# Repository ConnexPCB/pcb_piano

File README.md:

# pcb_piano
PCB with cap touch buttons that activate frequency generator

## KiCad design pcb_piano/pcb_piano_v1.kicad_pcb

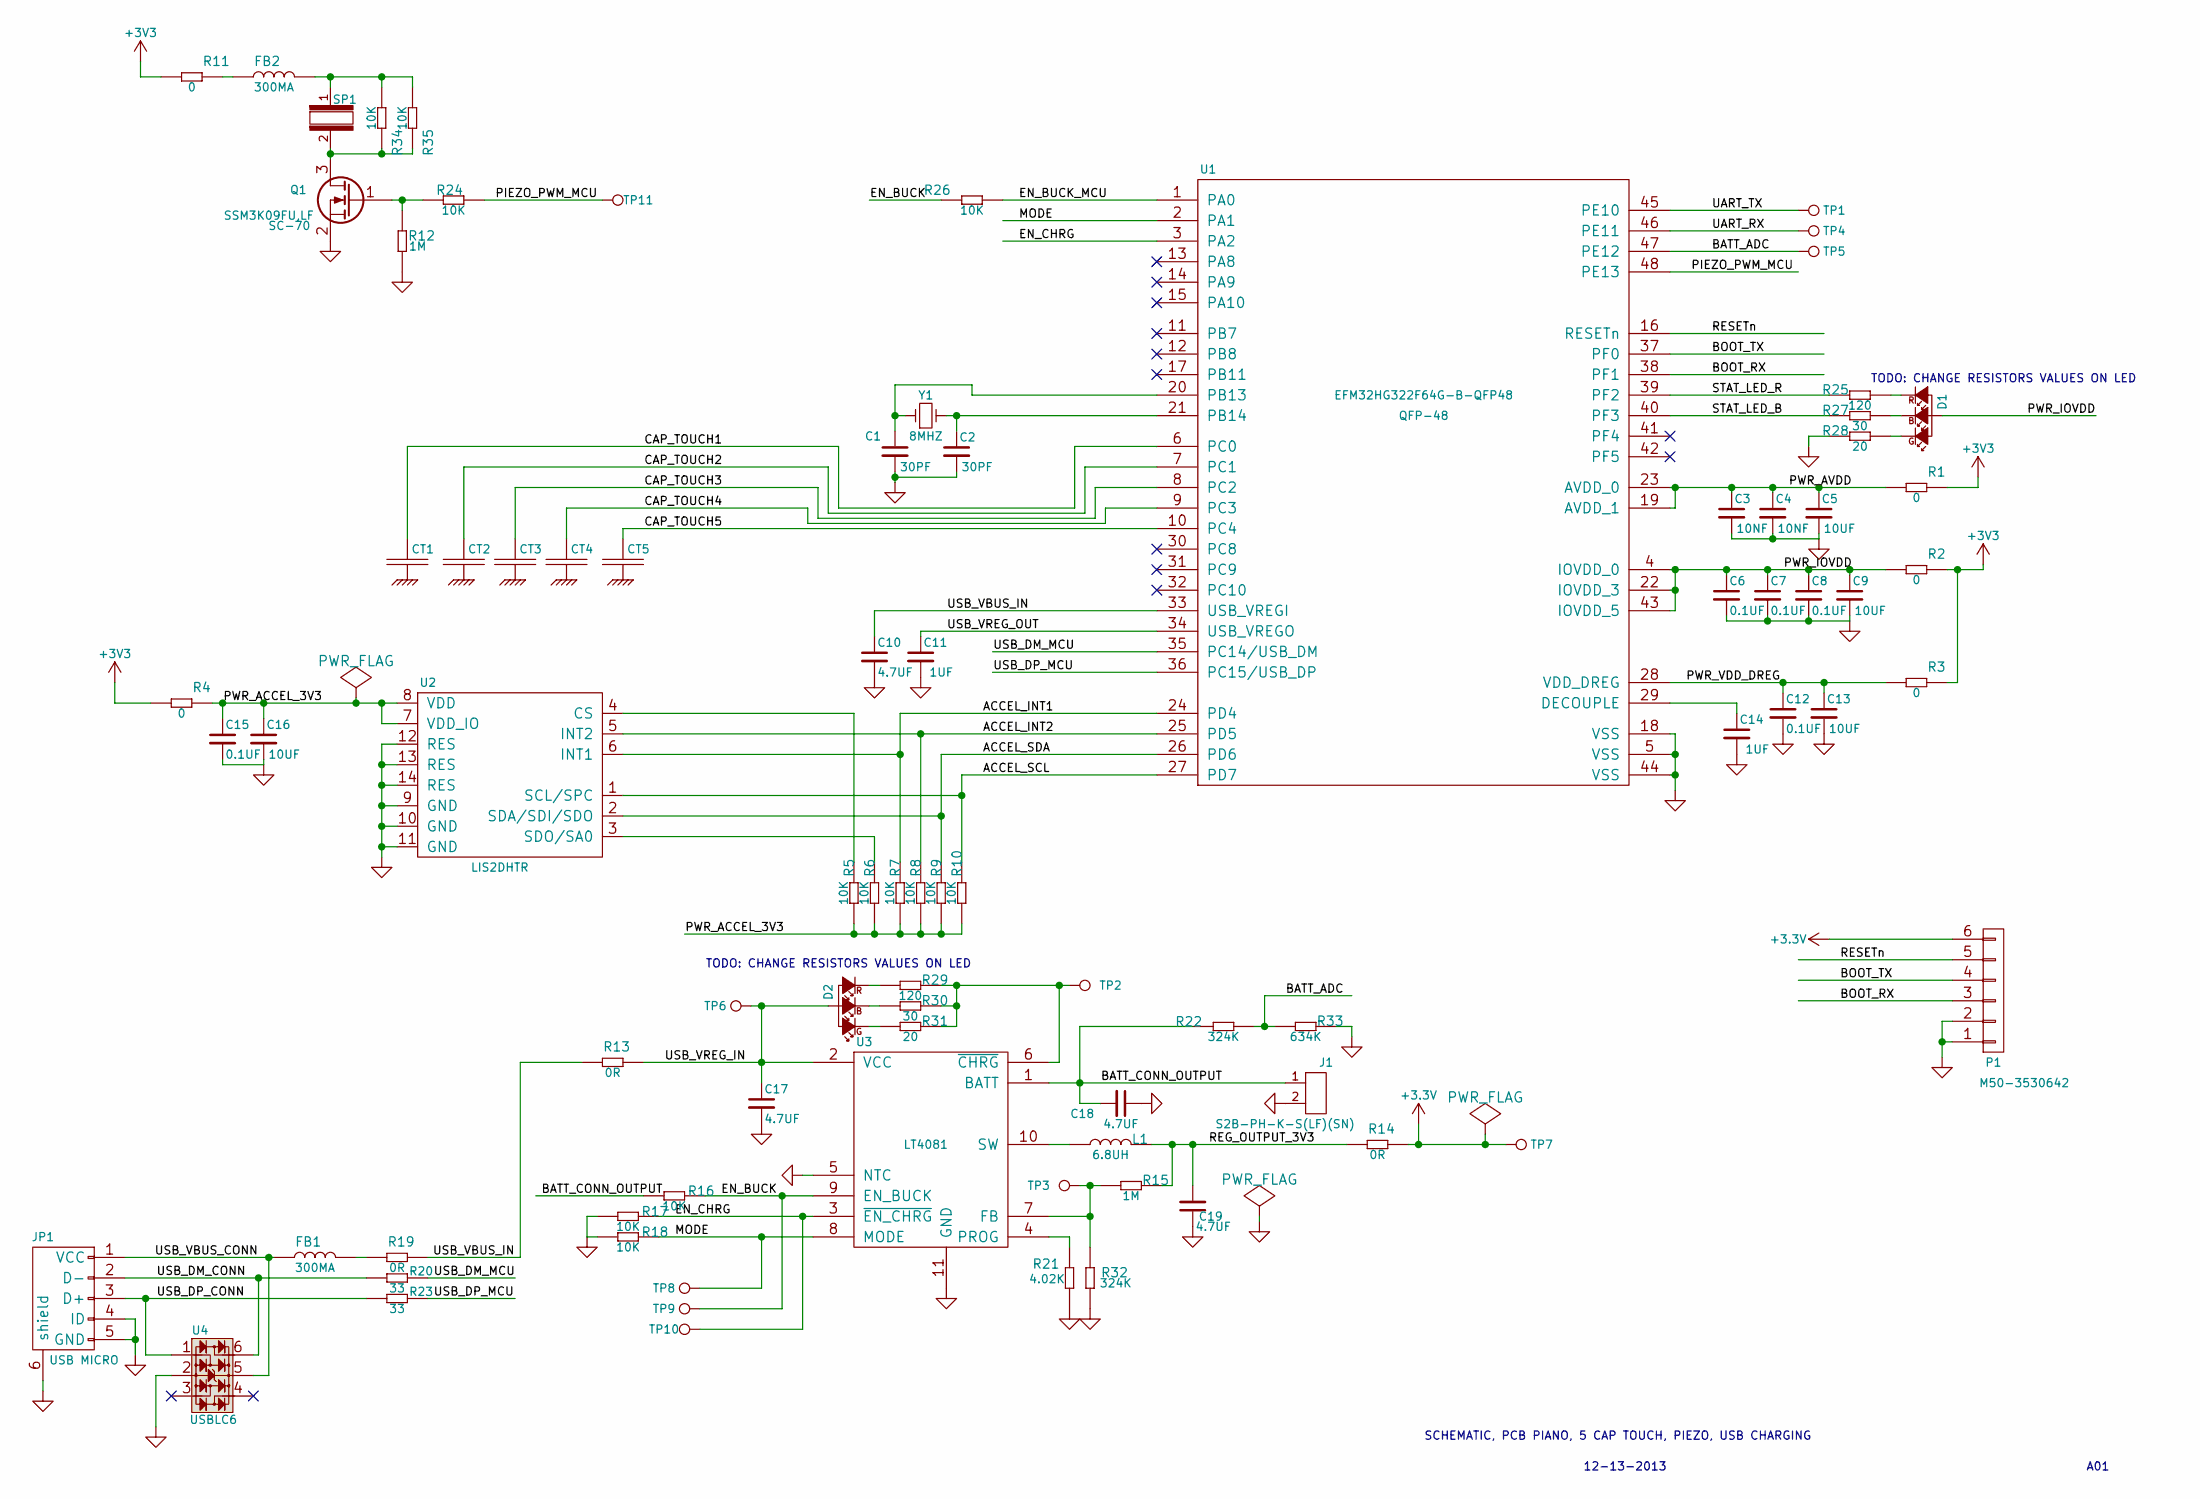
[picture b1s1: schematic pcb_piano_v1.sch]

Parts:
C1, C2: CONNEX-SMD-CAP-30PF-0402; C_0402; VOLTAGE 25V; MPN GRM1555C1E300JA01D
C3, C4: CONNEX-SMD-CAP-10NF-0402; C_0402; MPN GRM155R71C103KA01D
C5, C9, C13, C16: CONNEX-SMD-CAP-10UF-0402; C_0402; VOLTAGE 6.3V; MPN GRJ155R60J106ME11D
C6, C7, C8, C12, C15: CONNEX-SMD-CAP-100NF-0402; C_0402; MPN GRM155R71E104KE14D
C10, C17, C18, C19: CONNEX-SMD-CAP-4700NF-0603; C_0603; MPN GRM188R60J475ME19D
C11, C14: CONNEX-SMD-CAP-1UF-0402; C_0402; VOLTAGE 35V; MPN GRM155R6YA105KE11J
CT1, CT2, CT3, CT4, CT5: CONNEX-CAPTOUCH-BUTTON-SINGLE; CONNEX-CAPTOUCH-SINGLE-BUTTON-15MM; MPN NA
D1, D2: LED_RGB_SMLP34RGB1W3; led_0404_SMLP34RGB1W3; MPN SMLP34RGB1W3
FB1, FB2: CONNEX-SMD-FERRITE-BEAD-300MA-BLM15AG102SN1D; L_0402; MPN BLM15AG102SN1D
J1: CONNEX_CONN_2PIN_KEYED; CONNEX_CONN-2POS-KEYED-S2B-PH-K-S; MPN S2B-PH-K-S(LF)(SN)
JP1: connex_usb_micro_b_10103594-0001LF; USB_Micro-B_10103594-0001LF; MPN 10118194-0001LF
L1: CONNEX-SMD-INDUCTOR-6R8M-0603; L_0603; MPN GLFR1608T6R8M-LR
P1: CONN_01X06_M50-3530642; Pin_Header_Straight_1x06; MPN M50-3530642
Q1: Q_NMOS_SSM3K09FULF; SC-70; MPN SSM3K09FU,LF
R1, R2, R3, R4, R11: CONNEX-SMD-RES-0-0603; R_0603; MPN CRCW06030000Z0EAHP
R5, R6, R7, R8, R9, R10, R24, R34, R35: CONNEX-SMD-RES-10K-0603; R_0603; MPN CRCW060310K0FKEAHP
R12, R15: CONNEX-SMD-RES-1M-0603; R_0603; MPN RCG06031M00FKEA
R13, R14, R19: SMD-RES-0R-1_4W_0603_; R_0603; MPN CRCW06030000Z0EAHP
R16, R17, R18, R26: SMD-RES-10K-1%-1_10W_0603_; R_0603
R20, R23: CONNEX-SMD-RES-33-0402; R_0402; MPN ERJ-2RKF33R0X
R21: CONNEX-SMD-RES-4K02-0603; R_0603; MPN CRCW06034K02FKEA
R22, R32: CONNEX-SMD-RES-324K-0402; R_0402; MPN RC0402FR-07324KL
R25, R29: CONNEX-SMD-RES-120-0603; R_0603; MPN CRCW0603120RJNEA
R27, R30: CONNEX-SMD-RES-30-0603; R_0603; MPN CRCW060330R0JNEA
R28, R31: CONNEX-SMD-RES-20-0603; R_0603; MPN CRCW060320R0JNEA
R33: CONNEX-SMD-RES-634k-0402; R_0402; MPN ERJ-2RKF6343X
SP1: connex-piezo-4khz-AT-2440-TWT-R; CONNEX-PIEZO-AT-2440-TWT-R; MPN AT-2440-TWT-R
TP1, TP2, TP3, TP4, TP5, TP6, TP7, TP8, TP9, TP10, TP11: test_point_smt; TEST_POINT_SMD_50MIL; MPN na
U1: connex_EFM32HG322F64G-B-QFP48; TQFP-48_7x7mm_Pitch0.5mm; MPN EFM32HG322F64G-B-QFP48
U2: connex-accel-LIS2DHTR; CONNEX_LGA-14_2MMX2MM; MPN LIS2DHTR
U3: CONNEX_REGUL_LT4081; CONNEX_DFN_10PIN_3MMX3MM; MPN LTC4081EDD#PBF
U4: CONNEX-DIODE-TVS-USB-USBLC6-4SC6Y; SOT-23-6; MPN USBLC6-4SC6Y
Y1: Crystal_8MHZ_ABM3B-8.000MHZ-B2-T; CONNEX_CRYSTAL_4SMD_32X50; MPN ABM3B-8.000MHZ-B2-T

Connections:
/ACCEL_INT1: R7.2, U1.24 (PD4), U2.6 (INT1)
/ACCEL_INT2: R8.2, U1.25 (PD5), U2.5 (INT2)
/ACCEL_SCL: R10.2, U1.27 (PD7), U2.1 (SCL/SPC)
/ACCEL_SDA: R9.2, U1.26 (PD6), U2.2 (SDA/SDI/SDO)
/BATT_ADC: R22.1, R33.1, TP5.1, U1.47 (PE12)
/BATT_CONN_OUTPUT: C18.2, J1.1, R16.2, R22.2, U3.1 (BATT)
/BOOT_RX: P1.3, U1.38 (PF1)
/BOOT_TX: P1.4, U1.37 (PF0)
/CAP_TOUCH1: CT1.1, U1.6 (PC0)
/CAP_TOUCH2: CT2.1, U1.7 (PC1)
/CAP_TOUCH3: CT3.1, U1.8 (PC2)
/CAP_TOUCH4: CT4.1, U1.9 (PC3)
/CAP_TOUCH5: CT5.1, U1.10 (PC4)
/EN_BUCK: R16.1, R26.2, TP9.1, U3.9 (EN_BUCK)
/EN_BUCK_MCU: R26.1, U1.1 (PA0)
/EN_CHRG: R17.1, TP10.1, U1.3 (PA2), U3.3 (~EN_CHRG~)
/MODE: R18.1, TP8.1, U1.2 (PA1), U3.8 (MODE)
/PIEZO_PWM_MCU: R24.1, TP11.1, U1.48 (PE13)
/PWR_ACCEL_3V3: C15.1, C16.1, R4.2, R5.1, R6.1, R7.1, R8.1, R9.1, R10.1, U2.7 (VDD_IO), U2.8 (VDD)
/PWR_AVDD: C3.1, C4.1, C5.1, R1.1, U1.19 (AVDD_1), U1.23 (AVDD_0)
/PWR_IOVDD: C6.1, C7.1, C8.1, C9.1, D1.1, R2.1, U1.4 (IOVDD_0), U1.22 (IOVDD_3), U1.43 (IOVDD_5)
/PWR_VDD_DREG: C12.1, C13.1, R3.1, U1.28 (VDD_DREG)
/REG_OUTPUT_3V3: C19.2, L1.2, R14.1, R15.2
/RESETn: P1.5, U1.16 (RESETn)
/STAT_LED_B: R27.2, U1.40 (PF3)
/STAT_LED_R: R25.2, U1.39 (PF2)
/UART_RX: TP4.1, U1.46 (PE11)
/UART_TX: TP1.1, U1.45 (PE10)
/USB_DM_CONN: JP1.2 (D-), R20.1, U4.6 (IO4)
/USB_DM_MCU: R20.2, U1.35 (PC14/USB_DM)
/USB_DP_CONN: JP1.3 (D+), R23.1, U4.1 (IO1)
/USB_DP_MCU: R23.2, U1.36 (PC15/USB_DP)
/USB_VBUS_CONN: FB1.1, JP1.1 (VCC), U4.5 (VBUS)
/USB_VBUS_IN: C10.1, R13.1, R19.2, U1.33 (USB_VREGI)
/USB_VREG_IN: C17.1, D2.1, R13.2, TP6.1, U3.2 (VCC)
/USB_VREG_OUT: C11.1, U1.34 (USB_VREGO)
GND: C1.2, C2.2, C3.2, C4.2, C5.2, C6.2, C7.2, C8.2, C9.2, C10.2, C11.2, C12.2, C13.2, C14.2, C15.2, C16.2, C17.2, C18.1, C19.1, J1.2, JP1.4 (ID), JP1.5 (GND), JP1.6 (shield), P1.1, P1.2, Q1.2 (S), R12.2, R17.2, R18.2, R21.1, R28.2, R32.2, R33.2, U1.5 (VSS), U1.18 (VSS), U1.44 (VSS), U2.9 (GND), U2.10 (GND), U2.11 (GND), U2.12 (RES), U2.13 (RES), U2.14 (RES), U3.5 (NTC), U3.11 (GND), U4.2 (GND)
unnamed: C1.1, U1.20 (PB13), Y1.1
unnamed: C2.1, U1.21 (PB14), Y1.3
unnamed: C14.1, U1.29 (DECOUPLE)
unnamed: D1.2 (R), R25.1
unnamed: D1.3 (B), R27.1
unnamed: D1.4 (G), R28.1
unnamed: D2.2 (R), R29.1
unnamed: D2.3 (B), R30.1
unnamed: D2.4 (G), R31.1
unnamed: FB1.2, R19.1
unnamed: FB2.1, R11.2
unnamed: FB2.2, R34.1, R35.1, SP1.1
unnamed: L1.1, U3.10 (SW)
unnamed: Q1.1 (G), R12.1, R24.2
unnamed: Q1.3 (D), R34.2, R35.2, SP1.2
unnamed: R5.2, U2.4 (CS)
unnamed: R6.2, U2.3 (SDO/SA0)
unnamed: R15.1, R32.1, TP3.1, U3.7 (FB)
unnamed: R21.2, U3.4 (PROG)
unnamed: R29.2, R30.2, R31.2, TP2.1, U3.6 (~CHRG~)

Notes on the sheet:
SCHEMATIC, PCB PIANO, 5 CAP TOUCH, PIEZO, USB CHARGING
12-13-2013
A01
TODO: CHANGE RESISTORS VALUES ON LED

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
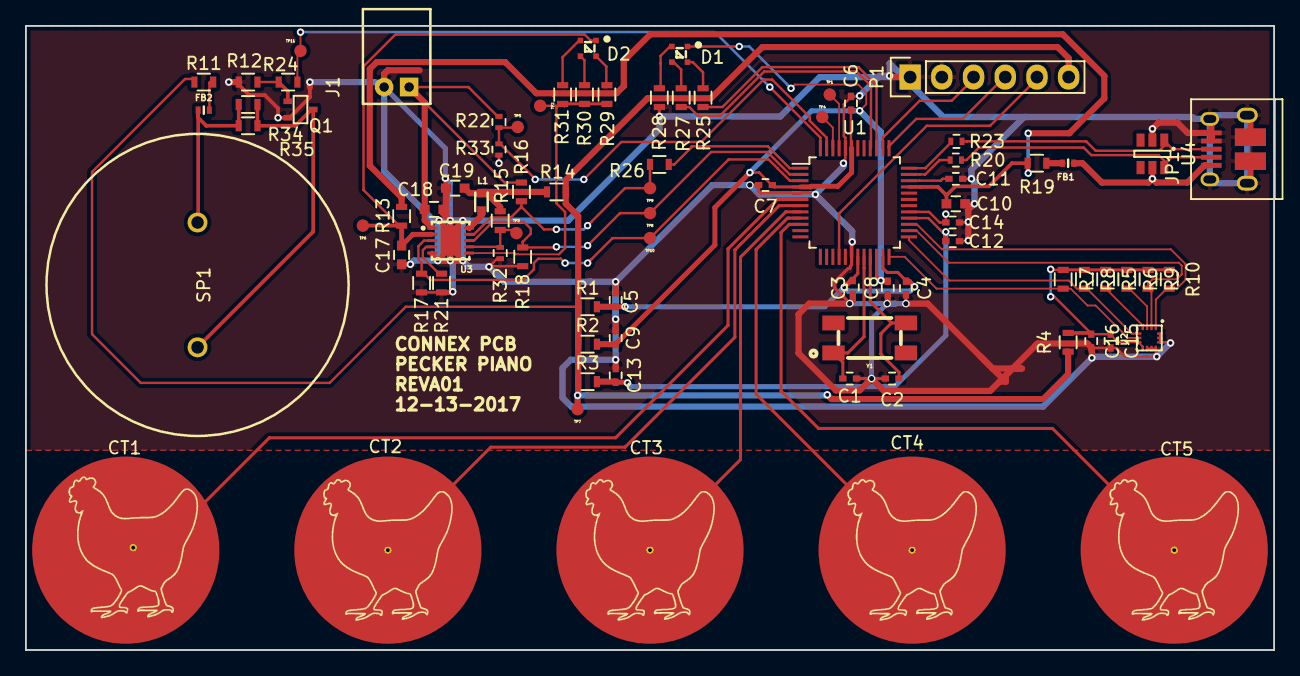
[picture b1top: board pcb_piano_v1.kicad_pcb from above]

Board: 2 copper layers, 100.0 x 50.0 mm, 85 parts (0 on the bottom side), 58 nets.

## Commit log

2017-12-12 Created kicad project for pcb_piano. Added connexPCB_libs submodule.
2017-12-13 Progress on schematic. Added happy gecko, regulator, and cap touch
2017-12-14 Added usb charging, ferrite bead, and piezo, began layout
2017-12-29 Pushed Version 1 hardware
2018-01-07 Mostly functional circular buffer with pwm. Though still has issues....
2018-01-07 Changed over to cpp files, created template for circular buffer
2018-01-13 Updated git ignore to be C and KiCAD
2018-01-13 Working version with PWM using DMA
2018-01-14 Note initialization to use sinusoid, and autoconfigure frequency based on PWM frequency (20khz)
2018-01-14 Cleaned up code from the previous debugging
2018-01-15 Working version with single button captouch using PRS and Timers to monitor in background
2018-01-15 Hacked together multitouch buttons
2018-01-27 Working version. Frequency calculation changed to be based on number of samples between 8 and 20 for 40kHz. Added top value to dutyCycle calculation (525) to prevent dutyCycle to be greater than top
2018-01-28 Non-working first conversion of leuart to dma
